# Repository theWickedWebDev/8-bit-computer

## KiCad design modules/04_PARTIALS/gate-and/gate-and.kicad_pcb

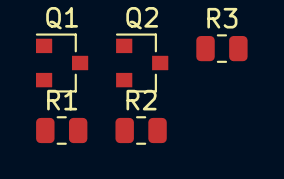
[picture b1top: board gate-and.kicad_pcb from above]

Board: 2 copper layers, 5 parts (0 on the bottom side), 4 nets, no tracks yet.

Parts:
Q1, Q2: PMBT2222; SOT-23
R1, R3: 10kohm; R_0805_2012Metric
R2: 3.9kohm; R_0805_2012Metric

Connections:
/Q: Q1.3, R2.1
unnamed: Q1.1, R3.2
unnamed: Q1.2, Q2.3
unnamed: Q2.1, R1.2

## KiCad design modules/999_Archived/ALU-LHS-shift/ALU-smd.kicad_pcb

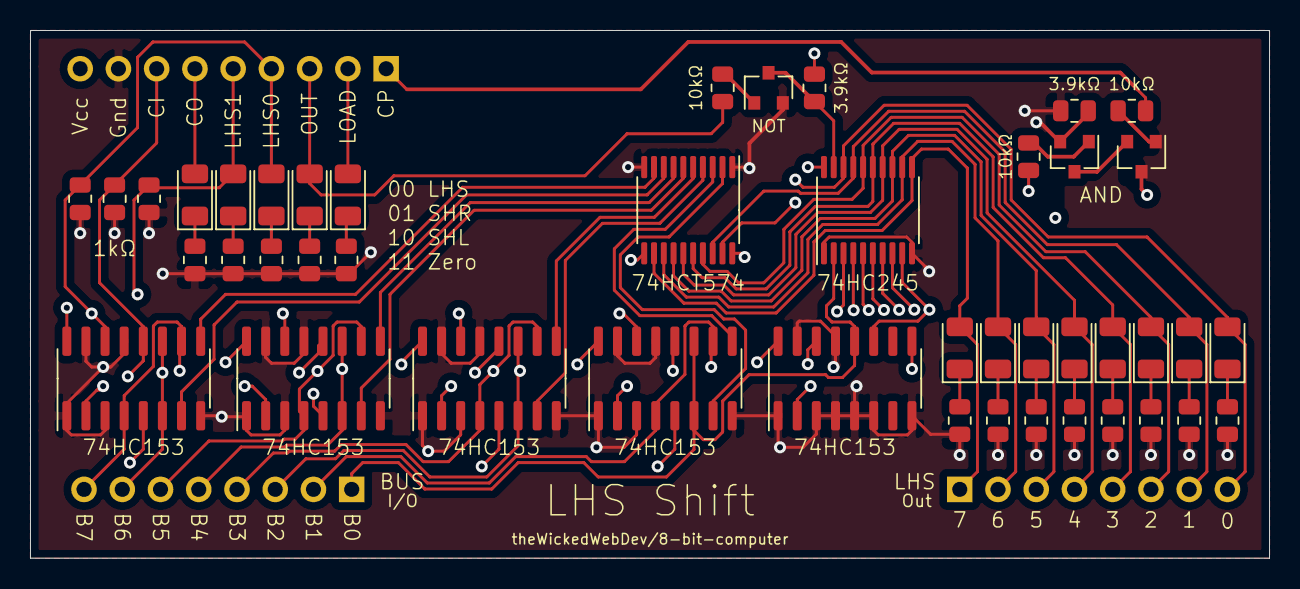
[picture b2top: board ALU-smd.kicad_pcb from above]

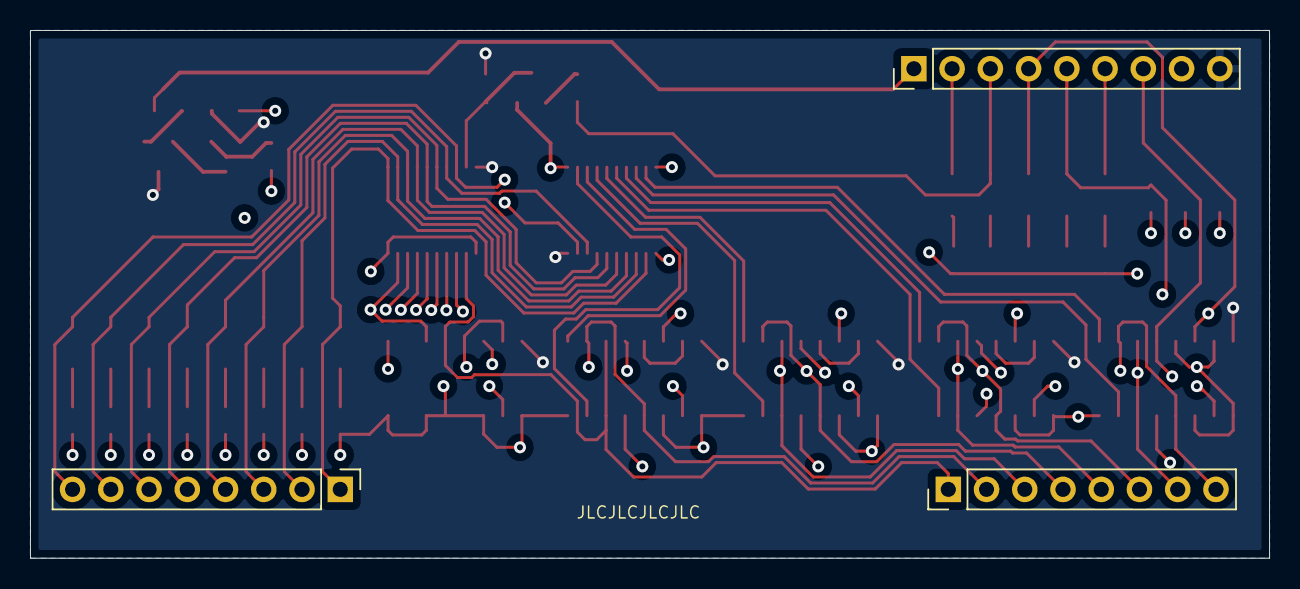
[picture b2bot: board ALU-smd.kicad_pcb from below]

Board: 4 copper layers, 82.3 x 35.1 mm, 47 parts (3 on the bottom side), 52 nets.

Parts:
J1: Conn_01x09; PinHeader_1x09_P2.54mm_Vertical
J2, J3: Conn_01x08; PinHeader_1x08_P2.54mm_Vertical
Q1, Q2, Q3: PMBT2222; SOT-23
R1, R2, R3, R4, R5, R6, R7, R8: 0402WGF1001TCE; R_0805_2012Metric
R9, R13: 0402WGF3901TCE; R_0805_2012Metric
R10, R11, R12: 0603WAF1002T5E; R_0805_2012Metric
U1, U3, U8, U38, U39: 19-217_BHC-ZL1M2RY_3T; LED_1206_3216Metric
U2, U4, U5, U6, U7, U9, U40, U41: 0603WAF1001T5E; R_0805_2012Metric
U23: 74HC574PW,118; TSSOP-20_4.4x6.5mm_P0.65mm
U24: 74HC245PW,118; TSSOP-20_4.4x6.5mm_P0.65mm
U25, U26, U27, U28, U29, U30, U31, U32: NCD0805R1; LED_1206_3216Metric
U33, U34, U35, U36, U37: 74HC153D,653; SOIC-16_3.9x9.9mm_P1.27mm

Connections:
/LHS - Shift/LHS_LOAD: Q1.2, R9.1, U23.11
/LHS - Shift/~LHS_OUT: Q3.3, R13.2, U24.19
/LHS_00: J2.8, U23.19, U24.18, U32.2
/LHS_01: J2.7, U23.18, U24.17, U31.2
/LHS_02: J2.6, U23.17, U24.16, U30.2
/LHS_03: J2.5, U23.16, U24.15, U29.2
/LHS_04: J2.4, U23.15, U24.14, U28.2
/LHS_05: J2.3, U23.14, U24.13, U27.2
/LHS_06: J2.2, U23.13, U24.12, U26.2
/LHS_07: J2.1, U23.12, U24.11, U25.2
BUS_00: J3.1, U24.2, U36.6, U36.11, U37.12
BUS_01: J3.2, U24.3, U35.5, U36.4, U36.10
BUS_02: J3.3, U24.4, U35.6, U35.11, U36.12
BUS_03: J3.4, U24.5, U34.5, U35.4, U35.10
BUS_04: J3.5, U24.6, U34.6, U34.11, U35.12
BUS_05: J3.6, U24.7, U33.5, U34.4, U34.10
BUS_06: J3.7, U24.8, U33.6, U33.11, U34.12
BUS_07: J3.8, U24.9, U33.4, U33.10, U37.11
CLOCK: J1.1, R11.1
GND: J1.8, Q3.2, R1.2, R2.2, R3.2, R4.2, R5.2, R6.2, R7.2, R8.2, R9.2, U2.1, U4.1, U5.2, U6.1, U7.1, U9.1, U23.1, U23.10, U24.1, U24.10, U33.1, U33.3, U33.8, U33.13, U33.15, U34.1, U34.3, U34.8, U34.13, U34.15, U35.1, U35.3, U35.8, U35.13, U35.15, U36.1, U36.3, U36.8, U36.13, U36.15, U37.1, U37.3, U37.4, U37.5, U37.6, U37.8, U37.13, U37.15, U40.1, U41.1
LHS_CARRY_IN: J1.7, U6.2, U33.12, U36.5
LHS_CARRY_OUT: J1.6, U1.2, U37.9
LHS_LOAD_IN: J1.2, R10.1, U3.2
LHS_OUT: J1.3, R12.1, U8.2
LHS_SEL_00: J1.4, U5.1, U33.14, U34.14, U35.14, U36.14, U37.14, U38.2
LHS_SEL_01: J1.5, U4.2, U33.2, U34.2, U35.2, U36.2, U37.2, U39.2
unnamed: Q1.1, R10.2
unnamed: Q1.3, Q2.2
unnamed: Q2.1, R11.2
unnamed: Q3.1, R12.2
unnamed: R1.1, U25.1
unnamed: R2.1, U26.1
unnamed: R3.1, U27.1
unnamed: R4.1, U28.1
unnamed: R5.1, U29.1
unnamed: R6.1, U30.1
unnamed: R7.1, U31.1
unnamed: R8.1, U32.1
unnamed: U1.1, U2.2
unnamed: U3.1, U7.2
unnamed: U8.1, U9.2
unnamed: U23.2, U36.7
unnamed: U23.3, U36.9
unnamed: U23.4, U35.7
unnamed: U23.5, U35.9
unnamed: U23.6, U34.7
unnamed: U23.7, U34.9
unnamed: U23.8, U33.7
unnamed: U23.9, U33.9
unnamed: U38.1, U40.2
unnamed: U39.1, U41.2
VCC: J1.9, Q2.3, R13.1, U23.20, U24.20, U33.16, U34.16, U35.16, U36.16, U37.16

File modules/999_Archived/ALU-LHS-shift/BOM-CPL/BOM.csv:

Designator,Value,LibPart,Footprint,Datasheet,C,Color,Description,JCLC,JLCPCB,L,R,V,,
C1,SMD-ECAP-5x5.8,Device:CP1_Small,Capacitor_SMD:CP_Elec_5x5.8,https://datasheet.lcsc.com/lcsc/1810010225_Lelon-VZS101M1ATR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,100µf,,"- - 5mm 100uF 10V -45℃~+105℃ ±20% 5.8mm 2000hrs 105℃ SMD,5x5.8mm Aluminum Electrolytic Capacitors - SMD ROHS",C140924,C140924,,,,,
C2,0603B103K500NT,JLCPCB:0603B103K500NT,Capacitor_SMD:C_0603_1608Metric,https://datasheet.lcsc.com/lcsc/2102081402_FH-Guangdong-Feng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,10nF,,X7R ±10% 50V 10nF 0603 Multilayer Ceramic Capacitors MLCC - SMD/SMT ROHS,C57112,,,,,,
C3,0603B103K500NT,JLCPCB:0603B103K500NT,Capacitor_SMD:C_0603_1608Metric,https://datasheet.lcsc.com/lcsc/2102081402_FH-Guangdong-Feng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,10nF,,X7R ±10% 50V 10nF 0603 Multilayer Ceramic Capacitors MLCC - SMD/SMT ROHS,C57112,,,,,,
C4,0603B103K500NT,JLCPCB:0603B103K500NT,Capacitor_SMD:C_0603_1608Metric,https://datasheet.lcsc.com/lcsc/2102081402_FH-Guangdong-Feng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,10nF,,X7R ±10% 50V 10nF 0603 Multilayer Ceramic Capacitors MLCC - SMD/SMT ROHS,C57112,,,,,,
C5,0603B103K500NT,JLCPCB:0603B103K500NT,Capacitor_SMD:C_0603_1608Metric,https://datasheet.lcsc.com/lcsc/2102081402_FH-Guangdong-Feng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,10nF,,X7R ±10% 50V 10nF 0603 Multilayer Ceramic Capacitors MLCC - SMD/SMT ROHS,C57112,,,,,,
J1,Conn_01x09,Connector_Generic:Conn_01x09,Connector_PinHeader_2.54mm:PinHeader_1x09_P2.54mm_Vertical,~,,,,,,,,,,
J2,Conn_01x08,Connector_Generic:Conn_01x08,Connector_PinHeader_2.54mm:PinHeader_1x08_P2.54mm_Vertical,~,,,,,,,,,,
J3,Conn_01x08,Connector_Generic:Conn_01x08,Connector_PinHeader_2.54mm:PinHeader_1x08_P2.54mm_Vertical,~,,,,,,,,,,
Q1,2N3904S-RTK_PS,JLCPCB:2N3904S-RTK_PS,Package_TO_SOT_SMD:SOT-23,https://www.onsemi.com/pub/Collateral/2N3903-D.PDF,,,,C18536,,2N3904,,,,
Q2,2N3904S-RTK_PS,JLCPCB:2N3904S-RTK_PS,Package_TO_SOT_SMD:SOT-23,https://www.onsemi.com/pub/Collateral/2N3903-D.PDF,,,,C18536,,2N3904,,,,
R1,0402WGF1001TCE,JLCPCB:0402WGF1001TCE,Resistor_SMD:R_0402_1005Metric,~,,,,C11702,,,,1kΩ,,
R2,0402WGF1001TCE,JLCPCB:0402WGF1001TCE,Resistor_SMD:R_0402_1005Metric,~,,,,C11702,,,,1kΩ,,
R3,0402WGF1001TCE,JLCPCB:0402WGF1001TCE,Resistor_SMD:R_0402_1005Metric,~,,,,C11702,,,,1kΩ,,
R4,0402WGF1001TCE,JLCPCB:0402WGF1001TCE,Resistor_SMD:R_0402_1005Metric,~,,,,C11702,,,,1kΩ,,
R5,0402WGF1001TCE,JLCPCB:0402WGF1001TCE,Resistor_SMD:R_0402_1005Metric,~,,,,C11702,,,,1kΩ,,
R6,0402WGF1001TCE,JLCPCB:0402WGF1001TCE,Resistor_SMD:R_0402_1005Metric,~,,,,C11702,,,,1kΩ,,
R7,0402WGF1001TCE,JLCPCB:0402WGF1001TCE,Resistor_SMD:R_0402_1005Metric,~,,,,C11702,,,,1kΩ,,
R8,0402WGF1001TCE,JLCPCB:0402WGF1001TCE,Resistor_SMD:R_0402_1005Metric,~,,,,C11702,,,,1kΩ,,
R9,0402WGF3901TCE,JLCPCB:0402WGF3901TCE,Resistor_SMD:R_0402_1005Metric,~,,,,C51721,,,3.9kΩ,,,
R10,0603WAF1002T5E,JLCPCB:0603WAF1002T5E,Resistor_SMD:R_0402_1005Metric,~,,,,C25804,,,10kΩ,,,
R11,0603WAF1002T5E,JLCPCB:0603WAF1002T5E,Resistor_SMD:R_0402_1005Metric,~,,,,C25804,,,10kΩ,,,
U2,0603WAF1001T5E,JLCPCB:0603WAF1001T5E,Resistor_SMD:R_0603_1608Metric,,,,,C21190,,,1KΩ,,,
U4,0603WAF1001T5E,JLCPCB:0603WAF1001T5E,Resistor_SMD:R_0603_1608Metric,,,,,C21190,,,1KΩ,,,
U5,0603WAF1001T5E,JLCPCB:0603WAF1001T5E,Resistor_SMD:R_0603_1608Metric,,,,,C21190,,,1KΩ,,,
U6,0603WAF1001T5E,JLCPCB:0603WAF1001T5E,Resistor_SMD:R_0603_1608Metric,,,,,C21190,,,1KΩ,,,
U23,"74HC574PW,118","JLCPCB:74HC574PW,118",Package_SO:TSSOP-20_4.4x6.5mm_P0.65mm,http://www.ti.com/lit/gpn/sn74LS574,,,,C93762,,74HC574,,,,
U24,"74HC245PW,118","JLCPCB:74HC245PW,118",Package_SO:TSSOP-20_4.4x6.5mm_P0.65mm,http://www.ti.com/lit/gpn/sn74LS245,,,,C5626,,,,,,
U25,NCD0805R1,JLCPCB:NCD0805R1,LED_SMD:LED_0805_2012Metric,,,RED,,C84256,,,,,,
U26,NCD0805R1,JLCPCB:NCD0805R1,LED_SMD:LED_0805_2012Metric,,,RED,,C84256,,,,,,
U27,NCD0805R1,JLCPCB:NCD0805R1,LED_SMD:LED_0805_2012Metric,,,RED,,C84256,,,,,,
U28,NCD0805R1,JLCPCB:NCD0805R1,LED_SMD:LED_0805_2012Metric,,,RED,,C84256,,,,,,
U29,NCD0805R1,JLCPCB:NCD0805R1,LED_SMD:LED_0805_2012Metric,,,RED,,C84256,,,,,,
U30,NCD0805R1,JLCPCB:NCD0805R1,LED_SMD:LED_0805_2012Metric,,,RED,,C84256,,,,,,
U31,NCD0805R1,JLCPCB:NCD0805R1,LED_SMD:LED_0805_2012Metric,,,RED,,C84256,,,,,,
U32,NCD0805R1,JLCPCB:NCD0805R1,LED_SMD:LED_0805_2012Metric,,,RED,,C84256,,,,,,
U33,"74HC153D,653","JLCPCB:74HC153D,653",Package_SO:SOIC-16_3.9x9.9mm_P1.27mm,http://www.ti.com/lit/gpn/sn74LS153,,,,C53334,,,,,,
U34,"74HC153D,653","JLCPCB:74HC153D,653",Package_SO:SOIC-16_3.9x9.9mm_P1.27mm,http://www.ti.com/lit/gpn/sn74LS153,,,,C53334,,,,,,
U35,"74HC153D,653","JLCPCB:74HC153D,653",Package_SO:SOIC-16_3.9x9.9mm_P1.27mm,http://www.ti.com/lit/gpn/sn74LS153,,,,C53334,,,,,,
U36,"74HC153D,653","JLCPCB:74HC153D,653",Package_SO:SOIC-16_3.9x9.9mm_P1.27mm,http://www.ti.com/lit/gpn/sn74LS153,,,,C53334,,,,,,
U37,"74HC153D,653","JLCPCB:74HC153D,653",Package_SO:SOIC-16_3.9x9.9mm_P1.27mm,http://www.ti.com/lit/gpn/sn74LS153,,,,C53334,,,,,,
U38,19-217_BHC-ZL1M2RY_3T,JLCPCB:19-217_BHC-ZL1M2RY_3T,LED_SMD:LED_0603_1608Metric,,,BLU,Blue 465~475nm 0603 Light Emitting Diodes (LED) ROHS,C72041,,,,,,
U39,19-217_BHC-ZL1M2RY_3T,JLCPCB:19-217_BHC-ZL1M2RY_3T,LED_SMD:LED_0603_1608Metric,,,BLU,Blue 465~475nm 0603 Light Emitting Diodes (LED) ROHS,C72041,,,,,,
U40,0603WAF1001T5E,JLCPCB:0603WAF1001T5E,Resistor_SMD:R_0603_1608Metric,,,,,C21190,,,1KΩ,,,
U41,0603WAF1001T5E,JLCPCB:0603WAF1001T5E,Resistor_SMD:R_0603_1608Metric,,,,,C21190,,,1KΩ,,,

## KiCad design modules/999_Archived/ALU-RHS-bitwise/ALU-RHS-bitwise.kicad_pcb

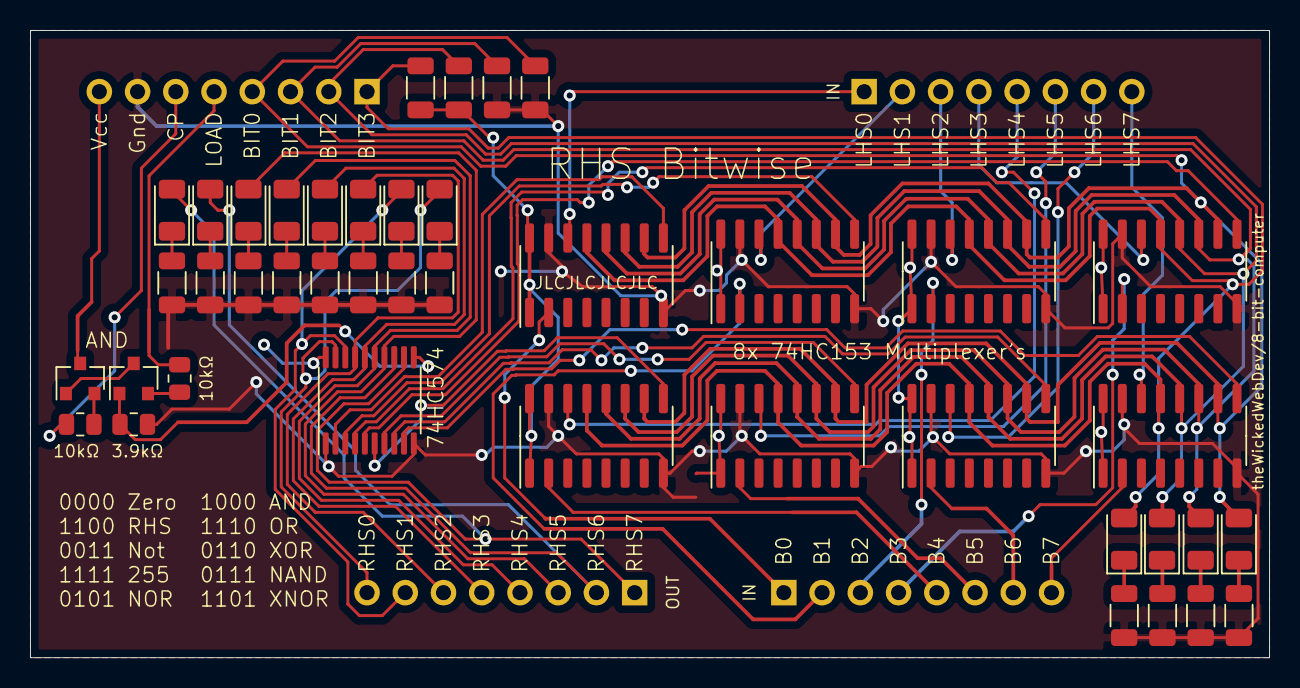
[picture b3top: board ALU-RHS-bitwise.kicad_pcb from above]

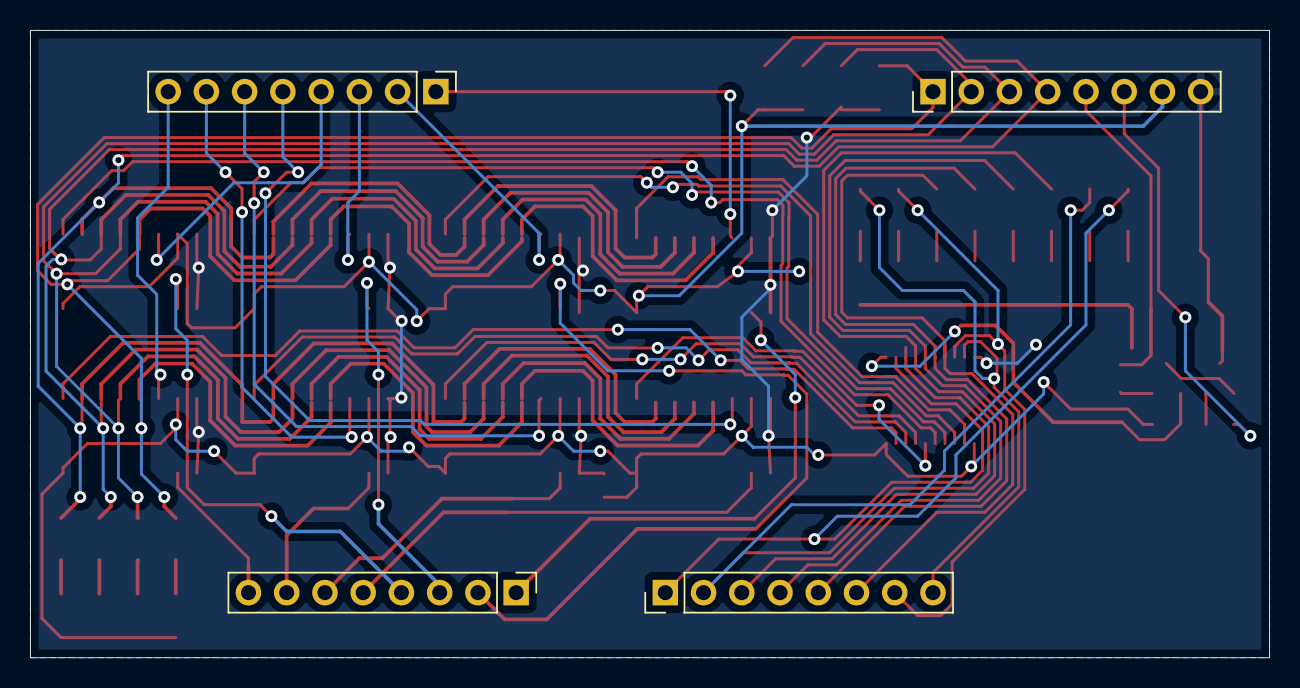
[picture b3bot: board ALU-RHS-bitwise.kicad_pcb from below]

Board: 2 copper layers, 82.3 x 41.7 mm, 46 parts (4 on the bottom side), 56 nets.

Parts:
J1, J2, J3, J4: Conn_01x08; PinHeader_1x08_P2.54mm_Vertical
Q1, Q2: 2N3904S-RTK_PS; SOT-23
R1, R2, R3, R4, R5, R6, R7, R8: 0402WGF1001TCE; R_1206_3216Metric
R9: 0402WGF3901TCE; R_0805_2012Metric
R10, R11: 0603WAF1002T5E; R_0805_2012Metric
U1, U26, U40, U41, U42, U43, U44, U45: 74HC153D,653; SOIC-16_3.9x9.9mm_P1.27mm
U2, U4, U6, U8, U10, U12, U14, U16: NCD0805R1; LED_1206_3216Metric
U27, U29, U31, U33: 19-217_BHC-ZL1M2RY_3T; LED_1206_3216Metric
U28, U30, U32, U34, U35, U36, U37, U38: 0603WAF1001T5E; R_1206_3216Metric
U46: 74HC574PW,118; TSSOP-20_4.4x6.5mm_P0.65mm

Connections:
/RHS Bitwise/LOAD: Q1.1, R9.1, U46.11
/RHS Bitwise/Q0: U1.9, U46.2
/RHS Bitwise/Q1: U40.9, U46.3
/RHS Bitwise/Q2: U42.9, U46.4
/RHS Bitwise/Q3: U44.9, U46.5
/RHS Bitwise/Q4: U26.9, U46.6
/RHS Bitwise/Q5: U41.9, U46.7
/RHS Bitwise/Q6: U43.9, U46.8
/RHS Bitwise/Q7: U45.9, U46.9
BIT0: J1.4, U1.10, U26.10, U27.2, U36.1, U40.10, U41.10, U42.10, U43.10, U44.10, U45.10
BIT1: J1.3, U1.11, U26.11, U29.2, U35.1, U40.11, U41.11, U42.11, U43.11, U44.11, U45.11
BIT2: J1.2, U1.12, U26.12, U31.2, U38.2, U40.12, U41.12, U42.12, U43.12, U44.12, U45.12
BIT3: J1.1, U1.13, U26.13, U33.2, U37.2, U40.13, U41.13, U42.13, U43.13, U44.13, U45.13
BUS0: J3.1, U1.2
BUS1: J3.2, U40.2
BUS2: J3.3, U42.2
BUS3: J3.4, U44.2
BUS4: J3.5, U26.2
BUS5: J3.6, U41.2
BUS6: J3.7, U43.2
BUS7: J3.8, U45.2
CLOCK: J1.6, R11.1
GND: J1.7, R1.2, R2.2, R3.2, R4.2, R5.2, R6.2, R7.2, R8.2, R9.2, U1.8, U1.15, U26.8, U26.15, U28.2, U30.2, U32.2, U34.1, U35.2, U36.2, U40.8, U40.15, U41.8, U41.15, U42.8, U42.15, U43.8, U43.15, U44.8, U44.15, U45.8, U45.15, U46.1, U46.10
LHS0: J2.1, U1.14
LHS1: J2.2, U40.14
LHS2: J2.3, U42.14
LHS3: J2.4, U44.14
LHS4: J2.5, U26.14
LHS5: J2.6, U41.14
LHS6: J2.7, U43.14
LHS7: J2.8, U45.14
unnamed: Q1.2, R10.2
unnamed: Q1.3, Q2.1
unnamed: Q2.2, R11.2
unnamed: R1.1, U2.1
unnamed: R2.1, U4.1
unnamed: R3.1, U6.1
unnamed: R4.1, U8.1
unnamed: R5.1, U10.1
unnamed: R6.1, U12.1
unnamed: R7.1, U14.1
unnamed: R8.1, U16.1
unnamed: U27.1, U28.1
unnamed: U29.1, U30.1
unnamed: U31.1, U32.1
unnamed: U33.1, U34.2
RHS0: J4.8, U16.2, U46.19
RHS1: J4.7, U14.2, U46.18
RHS2: J4.6, U12.2, U46.17
RHS3: J4.5, U10.2, U46.16
RHS4: J4.4, U8.2, U46.15
RHS5: J4.3, U6.2, U46.14
RHS6: J4.2, U4.2, U46.13
RHS7: J4.1, U2.2, U46.12
RHS_LOAD: J1.5, R10.1
VCC: J1.8, Q2.3, U1.1, U1.16, U26.1, U26.16, U37.1, U38.1, U40.1, U40.16, U41.1, U41.16, U42.1, U42.16, U43.1, U43.16, U44.1, U44.16, U45.1, U45.16, U46.20

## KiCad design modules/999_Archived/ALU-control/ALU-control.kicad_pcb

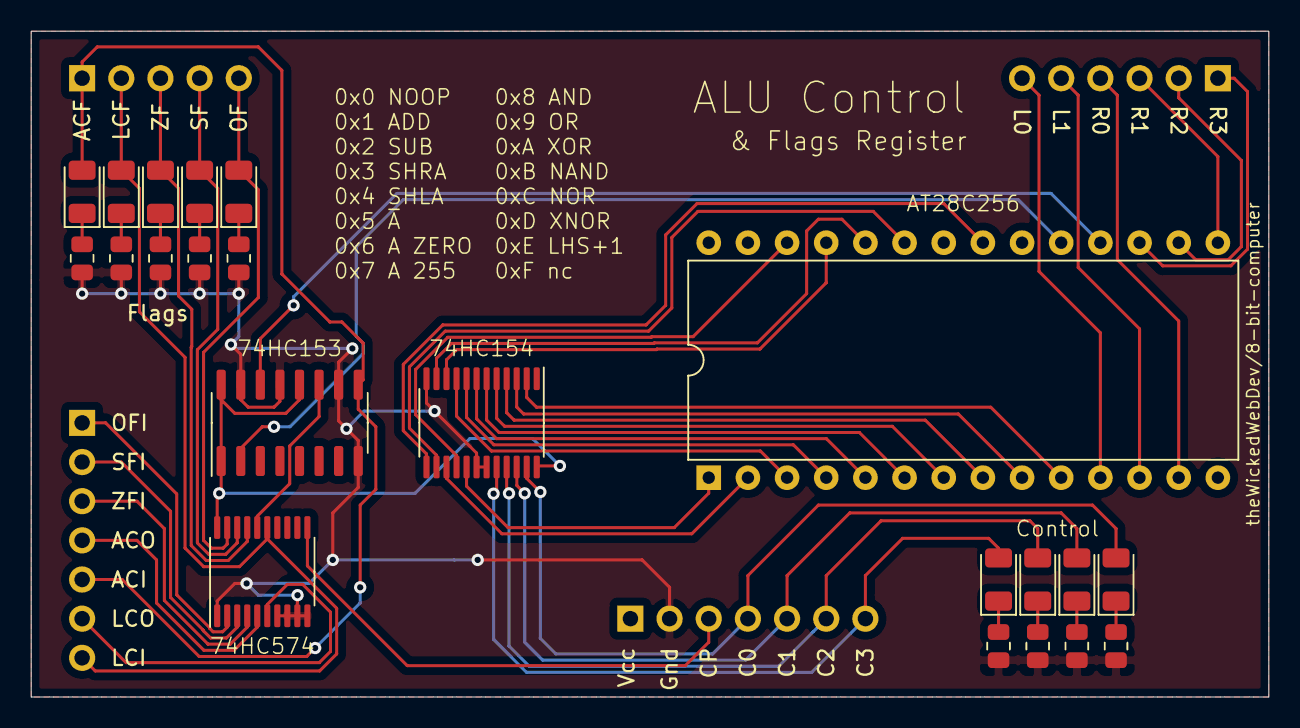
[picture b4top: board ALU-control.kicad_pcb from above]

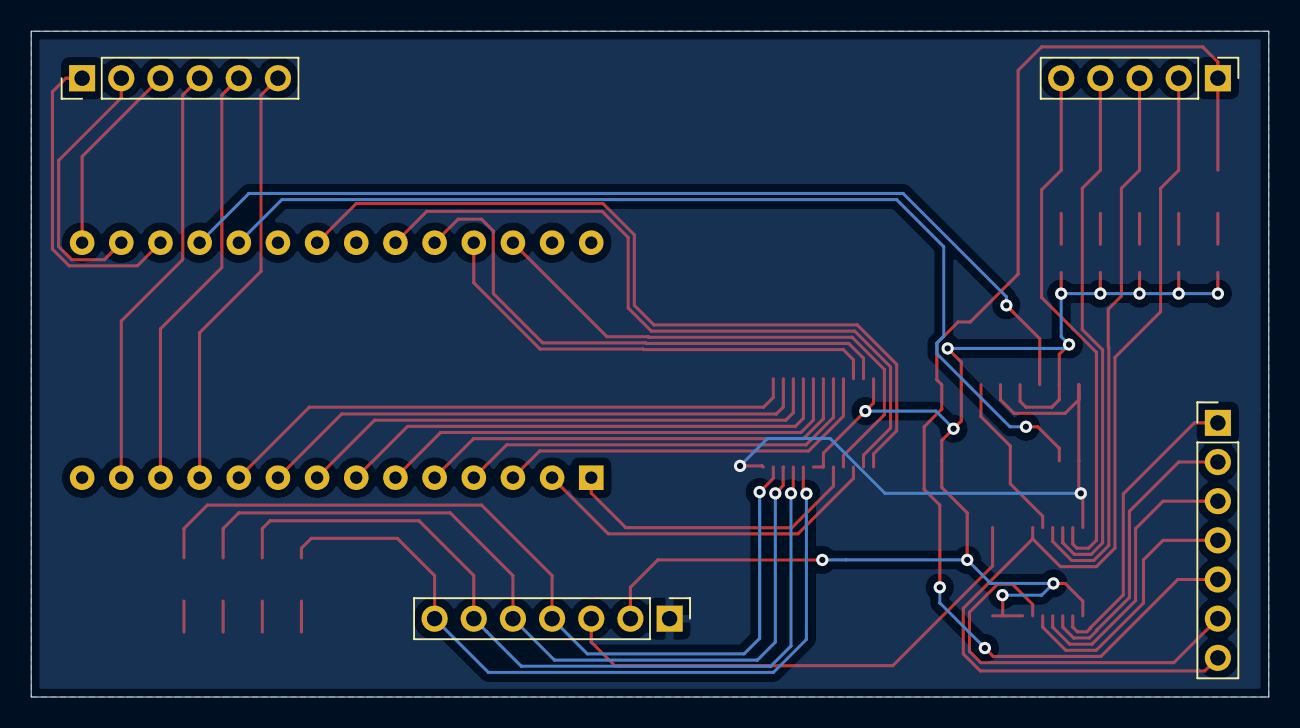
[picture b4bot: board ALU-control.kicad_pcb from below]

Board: 2 copper layers, 80.3 x 43.2 mm, 26 parts (4 on the bottom side), 50 nets.

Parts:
J1: Conn_01x06; PinHeader_1x06_P2.54mm_Vertical
J2, J3: Conn_01x07; PinHeader_1x07_P2.54mm_Vertical
J4: Conn_01x05; PinHeader_1x05_P2.54mm_Vertical
U1: 74HC154D,653; TSSOP-24_4.4x7.8mm_P0.65mm
U2: 28C256; DIP-28_W15.24mm
U3: 74HCT574; TSSOP-20_4.4x6.5mm_P0.65mm
U4: 74HC153D,653; SOIC-16_3.9x9.9mm_P1.27mm
U5, U7, U9, U11: 19-217_BHC-ZL1M2RY_3T; LED_1206_3216Metric
U6, U8, U10, U12, U14, U16, U18, U20, U22: 0603WAF1001T5E; R_0805_2012Metric
U13, U15, U17, U19, U21: 19-213_Y2C-CQ2R2L_3T(CY); LED_1206_3216Metric

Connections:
ADDER_CARRY_IN: J3.5, J4.1, U4.9, U21.2
ADDER_CARRY_OUT: J3.4, U3.5
ALU_CONTROL_0: J2.4, U1.23, U11.2
ALU_CONTROL_1: J2.5, U1.22, U9.2
ALU_CONTROL_2: J2.6, U1.21, U7.2
ALU_CONTROL_3: J2.7, U1.20, U5.2
CLOCK: J2.3, U3.11
CS0: U2.18, U4.14
CS1: U2.19, U4.2
GND: J2.2, U1.12, U1.18, U1.19, U3.1, U3.7, U3.8, U3.9, U3.10, U4.8, U4.10, U4.13, U4.15, U6.2, U8.2, U10.2, U12.2, U14.2, U16.2, U18.2, U20.2, U22.2
LHS0: J1.6, U2.11
LHS1: J1.5, U2.12
LHS_CARRY_IN: J3.7, J4.2, U3.15, U19.2
LHS_CARRY_OUT: J3.6, U3.6
unnamed: U1.2, U2.10
unnamed: U1.3, U2.9
unnamed: U1.4, U2.8
unnamed: U1.5, U2.7
unnamed: U1.6, U2.6
unnamed: U1.7, U2.5
unnamed: U1.8, U2.4
unnamed: U1.9, U2.3
unnamed: U1.10, U2.25
unnamed: U1.11, U2.24
unnamed: U1.13, U2.21
unnamed: U1.14, U2.23
unnamed: U1.15, U2.2
unnamed: U1.16, U2.26
unnamed: U1.17, U2.1
unnamed: U3.16, U4.11
unnamed: U5.1, U6.1
unnamed: U7.1, U8.1
unnamed: U9.1, U10.1
unnamed: U11.1, U12.1
unnamed: U13.1, U14.1
unnamed: U15.1, U16.1
unnamed: U17.1, U18.1
unnamed: U19.1, U20.1
unnamed: U21.1, U22.1
OVERFLOW_FLAG: J4.5, U3.19, U13.2
OVERFLOW_IN: J3.1, U3.2
RHS0: J1.4, U2.13
RHS1: J1.3, U2.15
RHS2: J1.2, U2.16
RHS3: J1.1, U2.17
SIGN_FLAG: J4.4, U3.18, U15.2
SIGN_IN: J3.2, U3.3
VCC: J2.1, U1.24, U3.20, U4.1, U4.12, U4.16
ZERO_FLAG: J4.3, U3.17, U17.2
ZERO_IN: J3.3, U3.4

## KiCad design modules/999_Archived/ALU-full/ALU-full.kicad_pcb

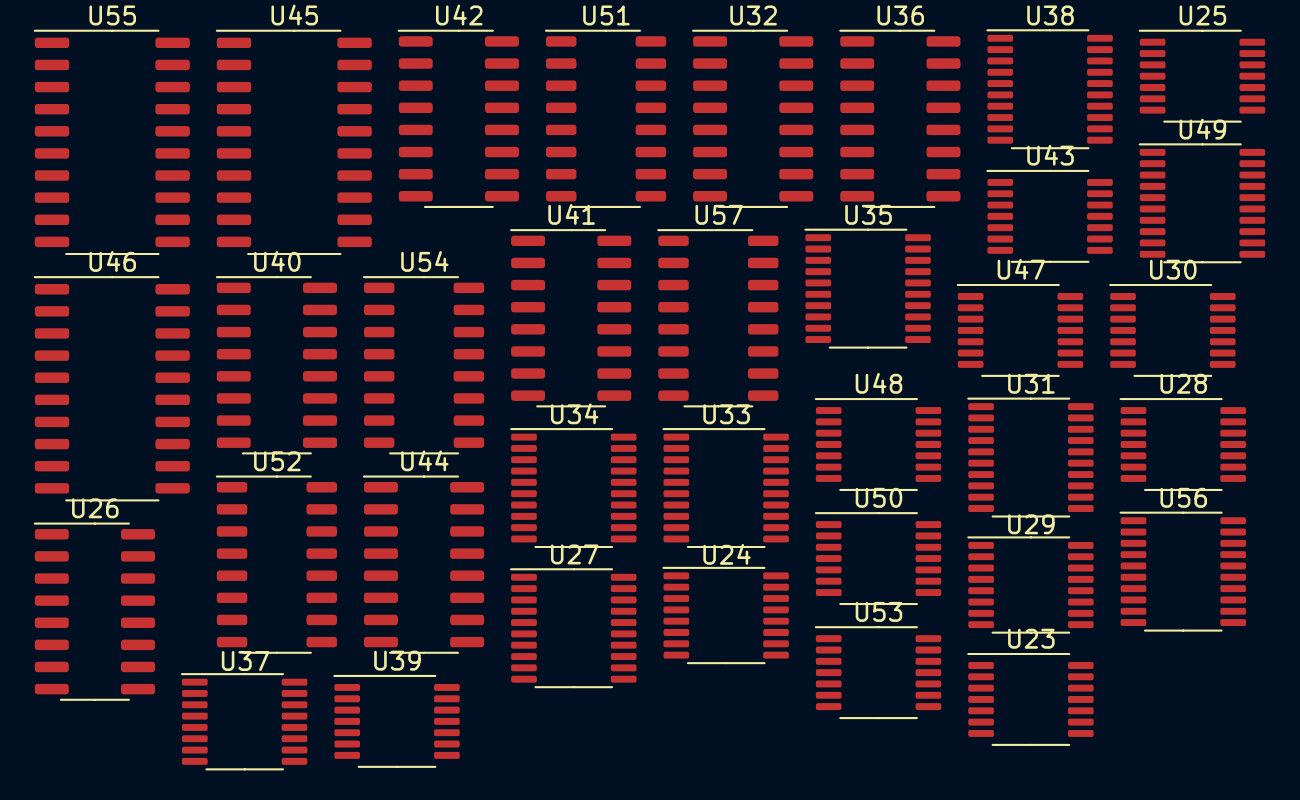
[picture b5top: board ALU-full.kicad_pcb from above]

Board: 2 copper layers, 35 parts (0 on the bottom side), 112 nets, no tracks yet.

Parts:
U23, U28: 74LS32; TSSOP-14_4.4x5mm_P0.65mm
U24, U29: 74LS86; TSSOP-16_4.4x5mm_P0.65mm
U25, U30: 74LS08; TSSOP-14_4.4x5mm_P0.65mm
U26, U32, U36, U40, U42: 74HC153D,653; SOIC-16_3.9x9.9mm_P1.27mm
U27, U31, U33, U34, U35, U38, U49, U56: 74HC245PW,118; TSSOP-20_4.4x6.5mm_P0.65mm
U37: 74LS138; TSSOP-16_4.4x5mm_P0.65mm
U39, U43: 74LS04; TSSOP-14_4.4x5mm_P0.65mm
U41, U44: 74LS157; SOIC-16_3.9x9.9mm_P1.27mm
U45: 74HC574PW,118; SO-20_5.3x12.6mm_P1.27mm
U46, U55: 74LS574; SO-20_5.3x12.6mm_P1.27mm
U47: 74LS02; TSSOP-14_4.4x5mm_P0.65mm
U48: 74HC86; TSSOP-14_4.4x5mm_P0.65mm
U50: 74HC86PW,118; TSSOP-14_4.4x5mm_P0.65mm
U51, U54: 74LS283; SO-16_3.9x9.9mm_P1.27mm
U52: 74LS21; SO-16_3.9x9.9mm_P1.27mm
U53: SN74HC08PWR; TSSOP-14_4.4x5mm_P0.65mm
U57: 74LS153; SO-16_3.9x9.9mm_P1.27mm

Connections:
/AND0: U25.3, U33.2
/AND1: U25.6, U33.3
/AND2: U25.8, U33.4
/AND3: U25.11, U33.5
/AND4: U30.3, U33.6
/AND5: U30.6, U33.7
/AND6: U30.8, U33.8
/AND7: U30.11, U33.9
/OR0: U23.3, U35.2
/OR1: U23.6, U35.3
/OR2: U23.8, U35.4
/OR3: U23.11, U35.5
/OR4: U28.3, U35.6
/OR5: U28.6, U35.7
/OR6: U28.8, U35.8
/OR7: U28.11, U35.9
/XOR0: U24.3, U34.2
/XOR1: U24.6, U34.3
/XOR2: U24.8, U34.4
/XOR3: U24.11, U34.5
/XOR4: U29.3, U34.6
/XOR5: U29.6, U34.7
/XOR6: U29.8, U34.8
/XOR7: U29.11, U34.9
A0: U23.2, U24.2, U25.2, U27.2, U45.19, U49.2, U51.5
A1: U23.5, U24.5, U25.5, U27.3, U45.18, U49.3, U51.3
A2: U23.10, U24.10, U25.10, U27.4, U45.17, U49.4, U51.14
A3: U23.13, U24.13, U25.13, U27.5, U45.16, U49.5, U51.12
A4: U27.6, U28.2, U29.2, U30.2, U45.15, U49.6, U54.5
A5: U27.7, U28.5, U29.5, U30.5, U45.14, U49.7, U54.3
A6: U27.8, U28.10, U29.10, U30.10, U45.13, U49.8, U54.14
A7: U27.9, U28.13, U29.13, U30.13, U45.12, U49.9, U50.2, U54.12
ADDER_CARRY_OUT: U54.9, U55.5
A_REG_IN_0: U40.7, U45.2
A_REG_IN_1: U40.9, U45.3
A_REG_IN_2: U36.7, U45.4
A_REG_IN_3: U36.9, U45.5
A_REG_IN_4: U32.7, U45.6
A_REG_IN_5: U32.9, U45.7
A_REG_IN_6: U26.7, U45.8
A_REG_IN_7: U26.9, U45.9
B0: U46.19, U51.6
B1: U46.18, U51.2
B2: U46.17, U51.15
B3: U46.16, U51.11
B4: U46.15, U54.6
B5: U46.14, U54.2
B6: U46.13, U54.15
B7: U46.12, U50.5, U54.11
BUS0: U23.1, U24.1, U25.1, U40.6, U40.11, U42.12, U49.18, U56.2
BUS1: U23.4, U24.4, U25.4, U36.5, U40.4, U40.10, U49.17, U56.3
BUS2: U23.9, U24.9, U25.9, U36.6, U36.11, U40.12, U49.16, U56.4
BUS3: U23.12, U24.12, U25.12, U32.5, U36.4, U36.10, U49.15, U56.5
BUS4: U28.1, U29.1, U30.1, U32.6, U32.11, U36.12, U49.14, U56.6
BUS5: U26.5, U28.4, U29.4, U30.4, U32.4, U32.10, U49.13, U56.7
BUS6: U26.6, U26.11, U28.9, U29.9, U30.9, U32.12, U49.12, U56.8
BUS7: U26.4, U26.10, U28.12, U29.12, U30.12, U42.11, U49.11, U56.9
B_REG0: U31.2, U41.4, U46.2
B_REG1: U31.3, U41.7, U46.3
B_REG2: U31.4, U41.9, U46.4
B_REG3: U31.5, U41.12, U46.5
B_REG4: U31.6, U44.4, U46.6
B_REG5: U31.7, U44.7, U46.7
B_REG6: U31.8, U44.9, U46.8
B_REG7: U31.9, U44.12, U46.9
CARRY_OUT_Shift: U42.9, U55.6
GND: U23.7, U24.7, U25.7, U26.1, U26.3, U26.8, U26.13, U26.15, U27.10, U28.7, U29.7, U30.7, U31.10, U32.1, U32.3, U32.8, U32.13, U32.15, U33.10, U34.10, U35.10, U36.1, U36.3, U36.8, U36.13, U36.15, U37.4, U37.5, U37.8, U38.2, U38.3, U38.4, U38.5, U38.6, U38.7, U38.8, U38.9, U38.10, U39.7, U40.1, U40.3, U40.8, U40.13, U40.15, U41.8, U41.15, U42.1, U42.3, U42.4, U42.5, U42.6, U42.8, U42.13, U42.15, U43.7, U44.8, U44.15, U45.1, U45.10, U46.1, U46.10, U47.7, U48.7, U49.10, U51.8, U54.8, U55.1, U55.7, U55.8, U55.9, U55.10, U56.10, U57.1, U57.3, U57.4, U57.8
INVERT: U41.1, U44.1
MUX0: U27.18, U31.18, U33.18, U34.18, U35.18, U38.18, U39.1, U41.2
MUX1: U27.17, U31.17, U33.17, U34.17, U35.17, U38.17, U39.3, U41.5
MUX2: U27.16, U31.16, U33.16, U34.16, U35.16, U38.16, U39.5, U41.11
MUX3: U27.15, U31.15, U33.15, U34.15, U35.15, U38.15, U39.9, U41.14
MUX4: U27.14, U31.14, U33.14, U34.14, U35.14, U38.14, U43.1, U44.2
MUX5: U27.13, U31.13, U33.13, U34.13, U35.13, U38.13, U43.3, U44.5
MUX6: U27.12, U31.12, U33.12, U34.12, U35.12, U38.12, U43.5, U44.11
MUX7: U27.11, U31.11, U33.11, U34.11, U35.11, U38.11, U43.9, U44.14
unnamed: U39.2, U41.3
unnamed: U39.4, U41.6
unnamed: U39.6, U41.10
unnamed: U39.8, U41.13
unnamed: U43.2, U44.3
unnamed: U43.4, U44.6
unnamed: U43.6, U44.10
unnamed: U43.8, U44.13
unnamed: U47.1, U52.1
unnamed: U47.4, U52.2
unnamed: U47.10, U52.4
unnamed: U47.13, U52.5
unnamed: U50.3, U53.12
unnamed: U50.6, U53.13
unnamed: U51.9, U54.7
unnamed: U52.6, U55.2
unnamed: U53.11, U55.4
unnamed: U55.16, U57.6
SEL_00_Shift: U26.14, U32.14, U36.14, U40.14, U42.14
SEL_01_Shift: U26.2, U32.2, U36.2, U40.2, U42.2
Shift_CARRY_OUT_FLAG: U26.12, U55.15
VCC: U23.14, U24.14, U25.14, U26.16, U27.1, U27.20, U28.14, U29.14, U30.14, U31.1, U31.20, U32.16, U33.1, U33.20, U34.1, U34.20, U35.1, U35.20, U36.16, U37.6, U37.16, U38.1, U38.20, U39.14, U40.16, U41.16, U42.16, U43.14, U44.16, U45.20, U46.20, U47.14, U48.14, U49.1, U49.20, U51.16, U54.16, U55.20, U56.1, U56.20, U57.5, U57.15, U57.16
~AND: U33.19, U37.14
~OR: U35.19, U37.13
~PASSA: U27.19, U37.11
~PASSB: U31.19, U37.15
~XOR: U34.19, U37.12
~ZERO: U37.10, U38.19
Σ0: U47.2, U51.4, U56.18
Σ1: U47.3, U51.1, U56.17
Σ2: U47.5, U51.13, U56.16
Σ3: U47.6, U51.10, U56.15
Σ4: U47.8, U54.4, U56.14
Σ5: U47.9, U54.1, U56.13
Σ6: U47.11, U54.13, U56.12
Σ7: U47.12, U50.1, U50.4, U54.10, U55.3, U56.11

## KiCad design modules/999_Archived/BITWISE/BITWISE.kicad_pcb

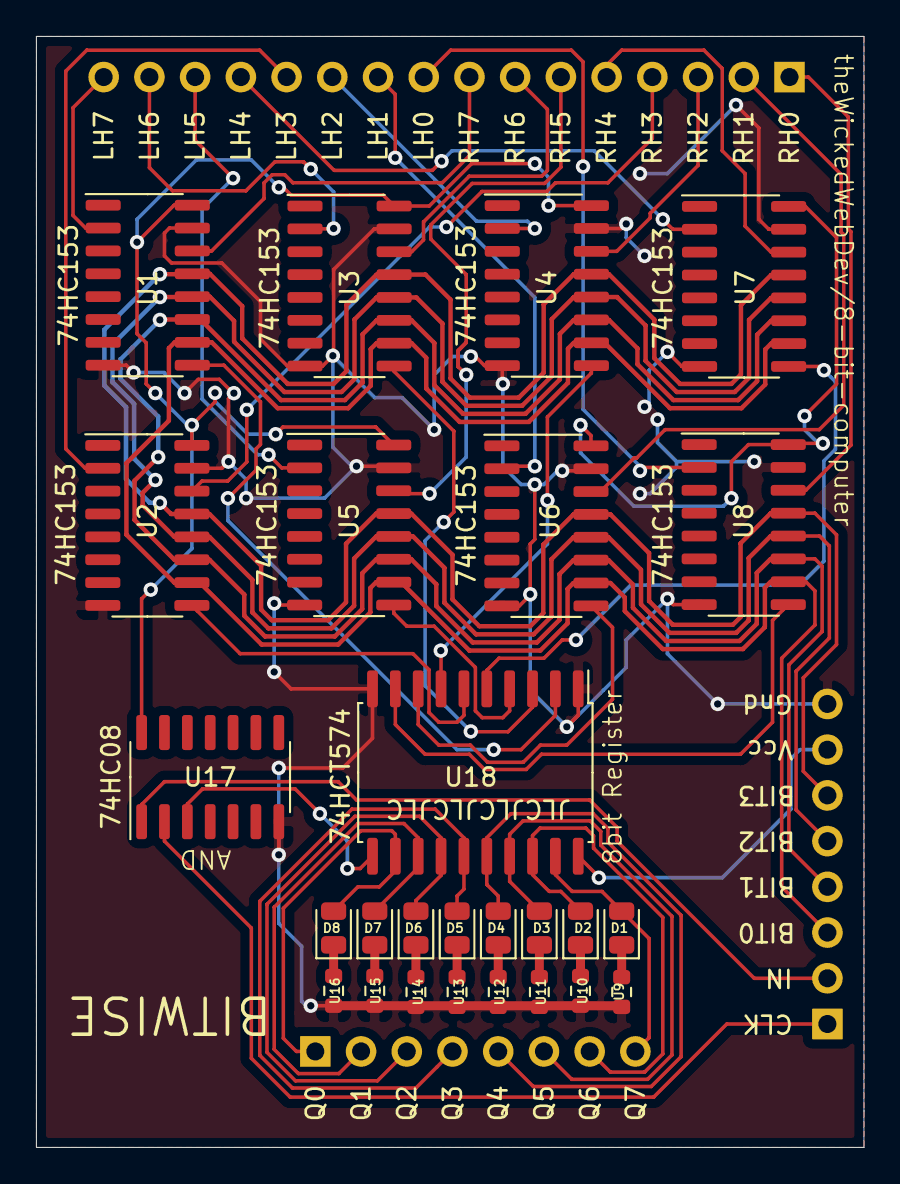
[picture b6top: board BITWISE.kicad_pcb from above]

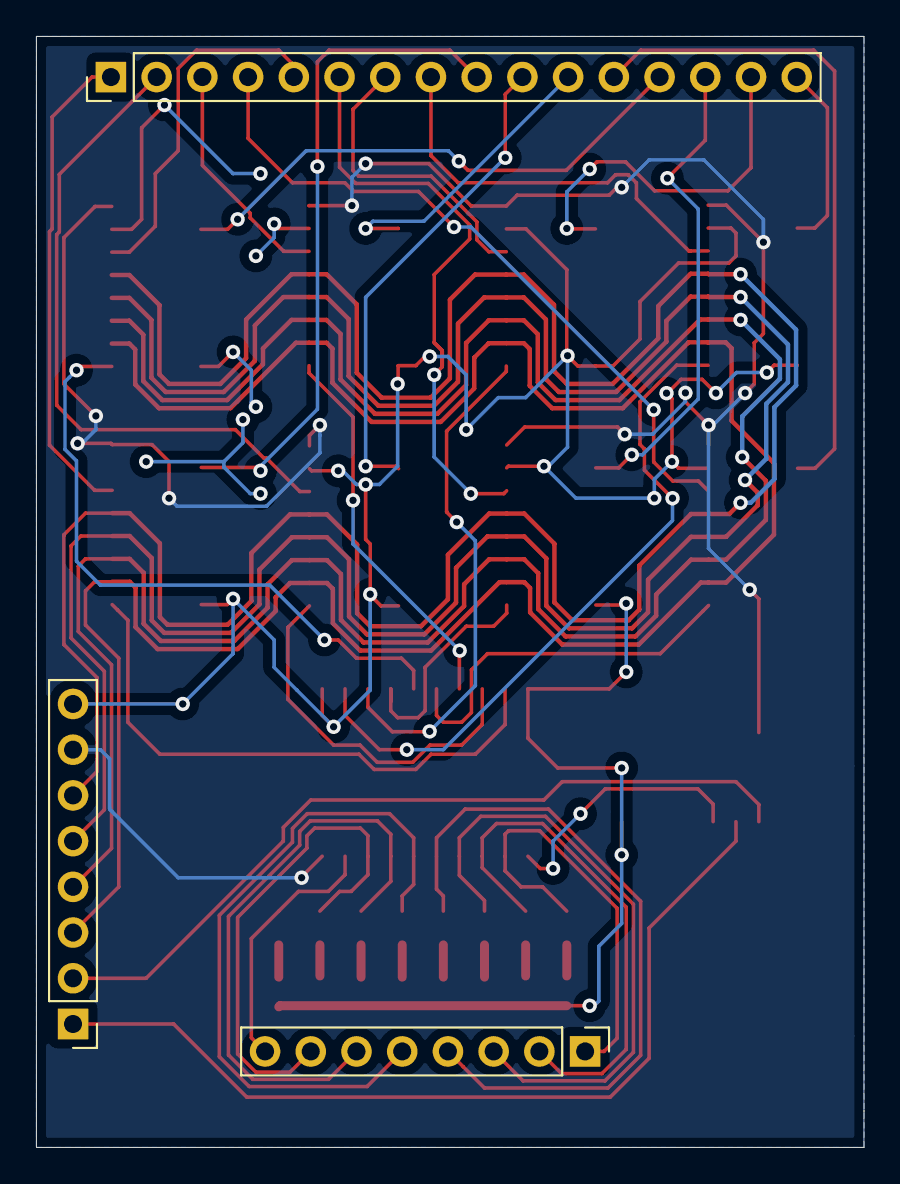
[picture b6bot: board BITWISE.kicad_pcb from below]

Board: 2 copper layers, 46.0 x 61.7 mm, 29 parts (3 on the bottom side), 49 nets.

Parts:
D1, D2, D3, D4, D5, D6, D7, D8: C2297; LED_0805_2012Metric
J1: Conn_01x16; PinHeader_1x16_P2.54mm_Vertical
J3, J4: Conn_01x08; PinHeader_1x08_P2.54mm_Vertical
U1, U2, U3, U4, U5, U6, U7, U8: 74HC153D,653; SOIC-16_3.9x9.9mm_P1.27mm
U9, U10, U11, U12, U13, U14, U15, U16: 0603WAF1001T5E; R_0603_1608Metric
U17: 74HC08D,653; SOIC-14_3.9x8.7mm_P1.27mm
U18: 74HCT574; SOIC-20W_7.5x12.8mm_P1.27mm

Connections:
A0: J1.9, U8.2
A1: J1.10, U6.2
A2: J1.11, U4.2
A3: J1.12, U2.2
A4: J1.13, U7.2
A5: J1.14, U5.2
A6: J1.15, U3.2
A7: J1.16, U1.2
B0: J1.1, U8.14
B1: J1.2, U6.14
B2: J1.3, U4.14
B3: J1.4, U2.14
B4: J1.5, U7.14
B5: J1.6, U5.14
B6: J1.7, U3.14
B7: J1.8, U1.14
BIT0: J4.3, U1.10, U2.10, U3.10, U4.10, U5.10, U6.10, U7.10, U8.10
BIT1: J4.4, U1.11, U2.11, U3.11, U4.11, U5.11, U6.11, U7.11, U8.11
BIT2: J4.5, U1.12, U2.12, U3.12, U4.12, U5.12, U6.12, U7.12, U8.12
BIT3: J4.6, U1.13, U2.13, U3.13, U4.13, U5.13, U6.13, U7.13, U8.13
CLOCK: J4.1, U17.2
GND: J4.8, U1.8, U1.15, U2.8, U2.15, U3.8, U3.15, U4.8, U4.15, U5.8, U5.15, U6.8, U6.15, U7.8, U7.15, U8.8, U8.15, U9.2, U10.2, U11.2, U12.2, U13.2, U14.2, U15.2, U16.2, U17.7, U18.1, U18.10
unnamed: D1.1, U9.1
unnamed: D2.1, U10.1
unnamed: D3.1, U11.1
unnamed: D4.1, U12.1
unnamed: D5.1, U13.1
unnamed: D6.1, U14.1
unnamed: D7.1, U15.1
unnamed: D8.1, U16.1
unnamed: U17.3, U18.11
Q0: U8.9, U18.9
Q1: U6.9, U18.8
Q2: U4.9, U18.7
Q3: U2.9, U18.6
Q4: U7.9, U18.5
Q5: U5.9, U18.4
Q6: U3.9, U18.3
Q7: U1.9, U18.2
RHS0: D8.2, J3.1, U18.12
RHS1: D7.2, J3.2, U18.13
RHS2: D6.2, J3.3, U18.14
RHS3: D5.2, J3.4, U18.15
RHS4: D4.2, J3.5, U18.16
RHS5: D3.2, J3.6, U18.17
RHS6: D2.2, J3.7, U18.18
RHS7: D1.2, J3.8, U18.19
RHS_IN: J4.2, U17.1
VCC: J4.7, U1.16, U2.16, U3.16, U4.16, U5.16, U6.16, U7.16, U8.16, U17.14, U18.20

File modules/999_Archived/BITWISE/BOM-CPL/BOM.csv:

Designator,Value,LibPart,Footprint,Datasheet,Color,Desc,JCLC,R,,
D1,C2297,JLCPCB:C2297,LED_SMD:LED_0805_2012Metric,~,GRN,520~530nm Green 0805 Light Emitting Diodes (LED) ROHS,C2297,,,
D2,C2297,JLCPCB:C2297,LED_SMD:LED_0805_2012Metric,~,GRN,520~530nm Green 0805 Light Emitting Diodes (LED) ROHS,C2297,,,
D3,C2297,JLCPCB:C2297,LED_SMD:LED_0805_2012Metric,~,GRN,520~530nm Green 0805 Light Emitting Diodes (LED) ROHS,C2297,,,
D4,C2297,JLCPCB:C2297,LED_SMD:LED_0805_2012Metric,~,GRN,520~530nm Green 0805 Light Emitting Diodes (LED) ROHS,C2297,,,
D5,C2297,JLCPCB:C2297,LED_SMD:LED_0805_2012Metric,~,GRN,520~530nm Green 0805 Light Emitting Diodes (LED) ROHS,C2297,,,
D6,C2297,JLCPCB:C2297,LED_SMD:LED_0805_2012Metric,~,GRN,520~530nm Green 0805 Light Emitting Diodes (LED) ROHS,C2297,,,
D7,C2297,JLCPCB:C2297,LED_SMD:LED_0805_2012Metric,~,GRN,520~530nm Green 0805 Light Emitting Diodes (LED) ROHS,C2297,,,
D8,C2297,JLCPCB:C2297,LED_SMD:LED_0805_2012Metric,~,GRN,520~530nm Green 0805 Light Emitting Diodes (LED) ROHS,C2297,,,
J1,Conn_01x16,Connector_Generic:Conn_01x16,Connector_PinHeader_2.54mm:PinHeader_1x16_P2.54mm_Vertical,~,,,,,,
J3,Conn_01x08,Connector_Generic:Conn_01x08,Connector_PinHeader_2.54mm:PinHeader_1x08_P2.54mm_Vertical,~,,,,,,
J4,Conn_01x08,Connector_Generic:Conn_01x08,Connector_PinHeader_2.54mm:PinHeader_1x08_P2.54mm_Vertical,~,,,,,,
U1,"74HC153D,653","JLCPCB:74HC153D,653",Package_SO:SOIC-16_3.9x9.9mm_P1.27mm,http://www.ti.com/lit/gpn/sn74LS153,,,C53334,,,
U2,"74HC153D,653","JLCPCB:74HC153D,653",Package_SO:SOIC-16_3.9x9.9mm_P1.27mm,http://www.ti.com/lit/gpn/sn74LS153,,,C53334,,,
U3,"74HC153D,653","JLCPCB:74HC153D,653",Package_SO:SOIC-16_3.9x9.9mm_P1.27mm,http://www.ti.com/lit/gpn/sn74LS153,,,C53334,,,
U4,"74HC153D,653","JLCPCB:74HC153D,653",Package_SO:SOIC-16_3.9x9.9mm_P1.27mm,http://www.ti.com/lit/gpn/sn74LS153,,,C53334,,,
U5,"74HC153D,653","JLCPCB:74HC153D,653",Package_SO:SOIC-16_3.9x9.9mm_P1.27mm,http://www.ti.com/lit/gpn/sn74LS153,,,C53334,,,
U6,"74HC153D,653","JLCPCB:74HC153D,653",Package_SO:SOIC-16_3.9x9.9mm_P1.27mm,http://www.ti.com/lit/gpn/sn74LS153,,,C53334,,,
U7,"74HC153D,653","JLCPCB:74HC153D,653",Package_SO:SOIC-16_3.9x9.9mm_P1.27mm,http://www.ti.com/lit/gpn/sn74LS153,,,C53334,,,
U8,"74HC153D,653","JLCPCB:74HC153D,653",Package_SO:SOIC-16_3.9x9.9mm_P1.27mm,http://www.ti.com/lit/gpn/sn74LS153,,,C53334,,,
U9,0603WAF1001T5E,JLCPCB:0603WAF1001T5E,Resistor_SMD:R_0603_1608Metric,,,,C21190,1KΩ,,
U10,0603WAF1001T5E,JLCPCB:0603WAF1001T5E,Resistor_SMD:R_0603_1608Metric,,,,C21190,1KΩ,,
U11,0603WAF1001T5E,JLCPCB:0603WAF1001T5E,Resistor_SMD:R_0603_1608Metric,,,,C21190,1KΩ,,
U12,0603WAF1001T5E,JLCPCB:0603WAF1001T5E,Resistor_SMD:R_0603_1608Metric,,,,C21190,1KΩ,,
U13,0603WAF1001T5E,JLCPCB:0603WAF1001T5E,Resistor_SMD:R_0603_1608Metric,,,,C21190,1KΩ,,
U14,0603WAF1001T5E,JLCPCB:0603WAF1001T5E,Resistor_SMD:R_0603_1608Metric,,,,C21190,1KΩ,,
U15,0603WAF1001T5E,JLCPCB:0603WAF1001T5E,Resistor_SMD:R_0603_1608Metric,,,,C21190,1KΩ,,
U16,0603WAF1001T5E,JLCPCB:0603WAF1001T5E,Resistor_SMD:R_0603_1608Metric,,,,C21190,1KΩ,,
U17,"74HC08D,653","JLCPCB:74HC08D,653",Package_SO:SOIC-14_3.9x8.7mm_P1.27mm,"https://datasheet.lcsc.com/lcsc/2006241032_Nexperia-74HC08D,653_C5593.pdf",,,C5593,,,
U18,74HCT574,JLCPCB:74HCT574,Package_SO:SOIC-20W_7.5x12.8mm_P1.27mm,http://www.ti.com/lit/gpn/sn74HCT574,,,C88576,,,
